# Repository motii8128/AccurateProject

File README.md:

# AccurateProject
2025年部内ロボコン「キアイダケ」チームのソフトウェア、ハードウェアについて

|name|link|
|:--:|:--:|
|マイコンソフトウェア|[AccurateHardware](https://github.com/motii8128/AccurateProject/tree/main/AccurateHardware)|
|制御基盤|[AccurateBoard](https://github.com/motii8128/AccurateProject/tree/main/Accurate)|
|電源基盤|[MainPowerSupplyer](https://github.com/motii8128/AccurateProject/tree/main/MainPowerSuppky)|
|分電基盤|[PowerDivider](https://github.com/motii8128/AccurateProject/tree/main/PowerDivider)|
|LED基盤|[led01](https://github.com/motii8128/AccurateProject/tree/main/led01)|

# マイコンソフトウェア「AccurateHardware」

# マイコン制御基盤「AccurateBoard」

# 電源基盤「MainPowerSupplyer」

# 分電基盤「PowerDivider」

# LED基盤「led01」

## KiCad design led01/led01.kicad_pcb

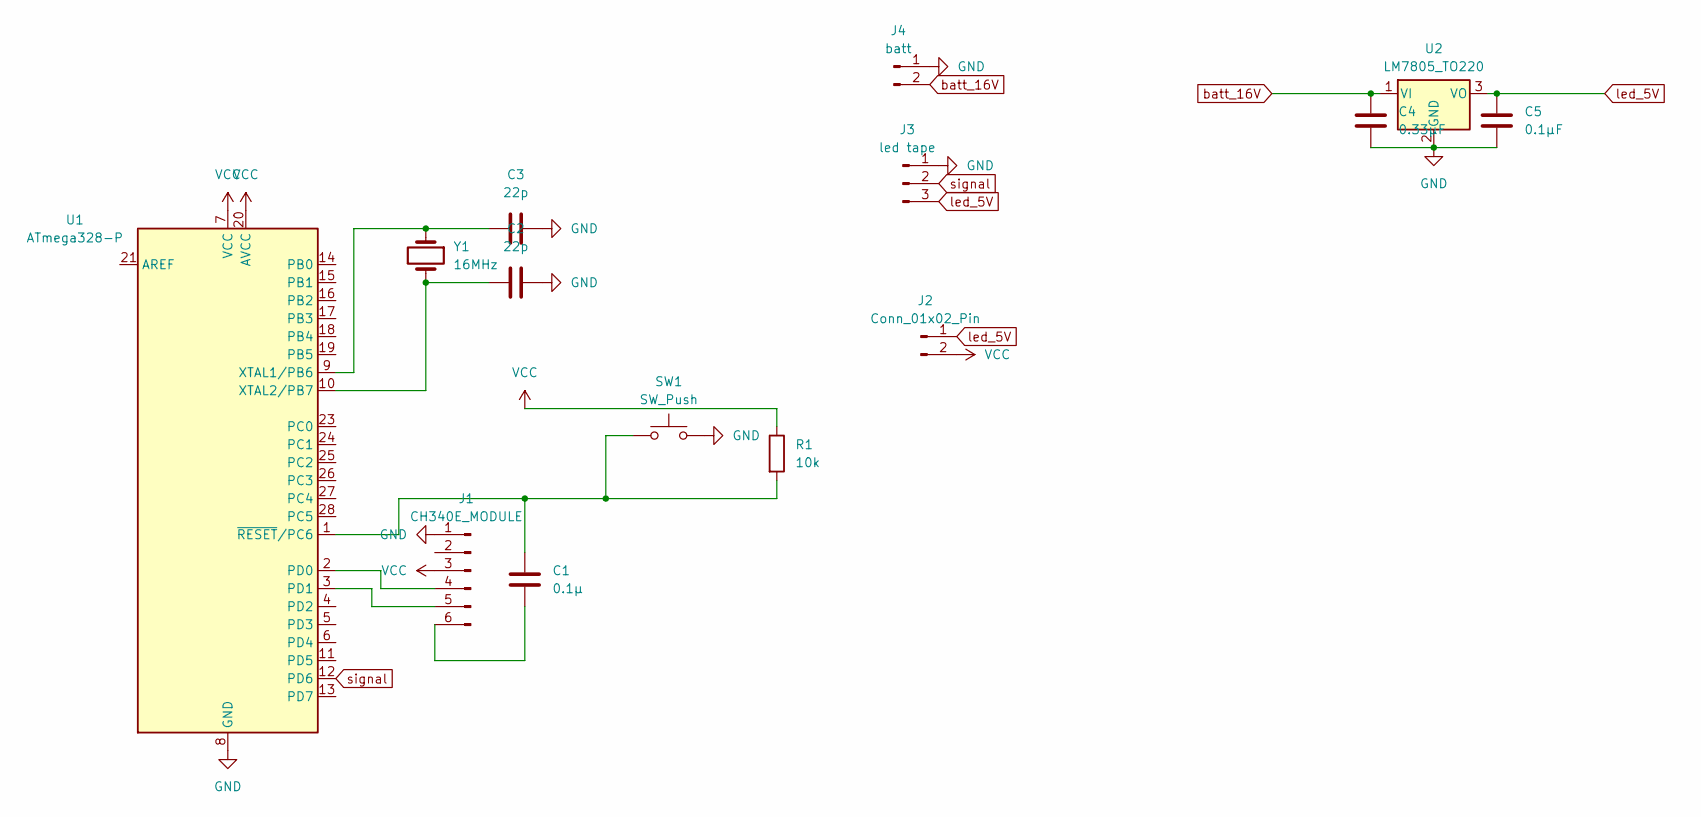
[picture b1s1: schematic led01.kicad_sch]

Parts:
C1: 0.1μ; C_Disc_D3.0mm_W2.0mm_P2.50mm
C2, C3: 22p; C_Disc_D3.0mm_W2.0mm_P2.50mm
C4: 0.33μF; C_Disc_D3.0mm_W2.0mm_P2.50mm
C5: 0.1μF; C_Disc_D3.0mm_W2.0mm_P2.50mm
J1: CH340E_MODULE; PinHeader_1x06_P2.54mm_Vertical
J2: Conn_01x02_Pin; PinHeader_1x02_P2.54mm_Vertical
J3: led tape; JST_XH_S3B-XH-A-1_1x03_P2.50mm_Horizontal
J4: batt; AMASS_XT30PW-M_1x02_P2.50mm_Horizontal
R1: 10k; R_Axial_DIN0207_L6.3mm_D2.5mm_P10.16mm_Horizontal
SW1: SW_Push; SW_PUSH_6mm
U1: ATmega328-P; DIP-28_W7.62mm
U2: LM7805_TO220; TO-220-3_Vertical
Y1: 16MHz; Crystal_HC18-U_Vertical

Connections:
GND: C2.2, C3.2, C4.2, C5.2, J1.1, J3.1, J4.1, SW1.2, U1.8 (GND), U1.22 (GND), U2.2 (GND)
unnamed: J1.4, U1.2 (PD0)
unnamed: J1.5, U1.3 (PD1)
unnamed: C1.2, J1.6
unnamed: C3.1, U1.9 (XTAL1/PB6), Y1.1
unnamed: C2.1, U1.10 (XTAL2/PB7), Y1.2
unnamed: C1.1, R1.2, SW1.1, U1.1 (~RESET/PC6)
VCC: J1.3, J2.2, R1.1, U1.7 (VCC), U1.20 (AVCC)
batt_16V: C4.1, J4.2, U2.1 (VI)
led_5V: C5.1, J2.1, J3.3, U2.3 (VO)
signal: J3.2, U1.12 (PD6)

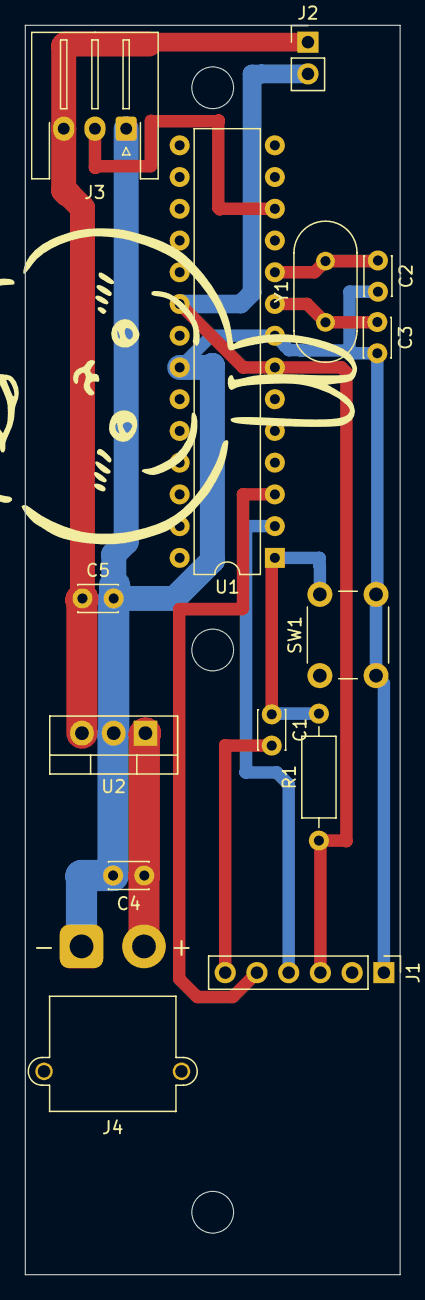
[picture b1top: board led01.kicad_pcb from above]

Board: 2 copper layers, 30.0 x 100.0 mm, 14 parts (0 on the bottom side), 11 nets.

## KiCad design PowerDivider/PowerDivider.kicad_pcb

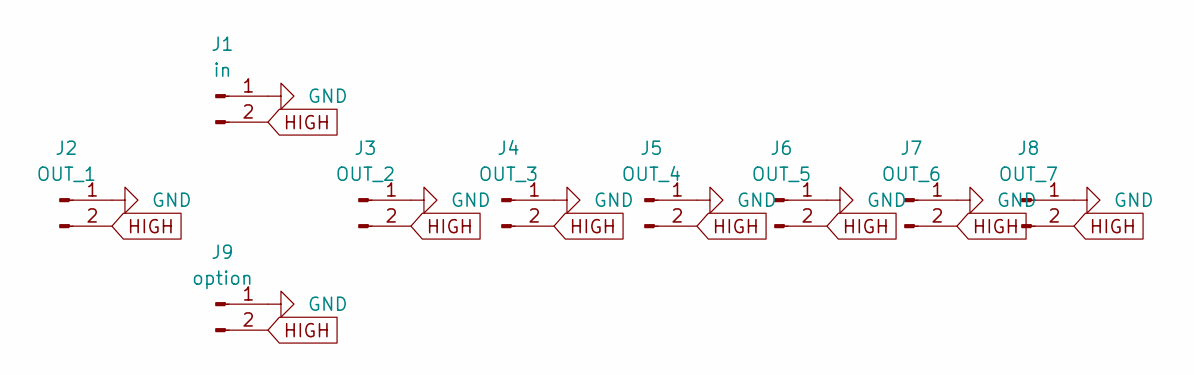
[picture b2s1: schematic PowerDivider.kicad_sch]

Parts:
J1: in; AMASS_XT30PW-M_1x02_P2.50mm_Horizontal
J2: OUT_1; AMASS_XT30PW-F_1x02_P2.50mm_Horizontal
J3: OUT_2; AMASS_XT30PW-F_1x02_P2.50mm_Horizontal
J4: OUT_3; AMASS_XT30PW-F_1x02_P2.50mm_Horizontal
J5: OUT_4; AMASS_XT30PW-F_1x02_P2.50mm_Horizontal
J6: OUT_5; AMASS_XT30PW-F_1x02_P2.50mm_Horizontal
J7: OUT_6; AMASS_XT30PW-F_1x02_P2.50mm_Horizontal
J8: OUT_7; AMASS_XT30PW-F_1x02_P2.50mm_Horizontal
J9: option; AMASS_XT30PW-M_1x02_P2.50mm_Horizontal

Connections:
GND: J1.1, J2.1, J3.1, J4.1, J5.1, J6.1, J7.1, J8.1, J9.1
HIGH: J1.2, J2.2, J3.2, J4.2, J5.2, J6.2, J7.2, J8.2, J9.2

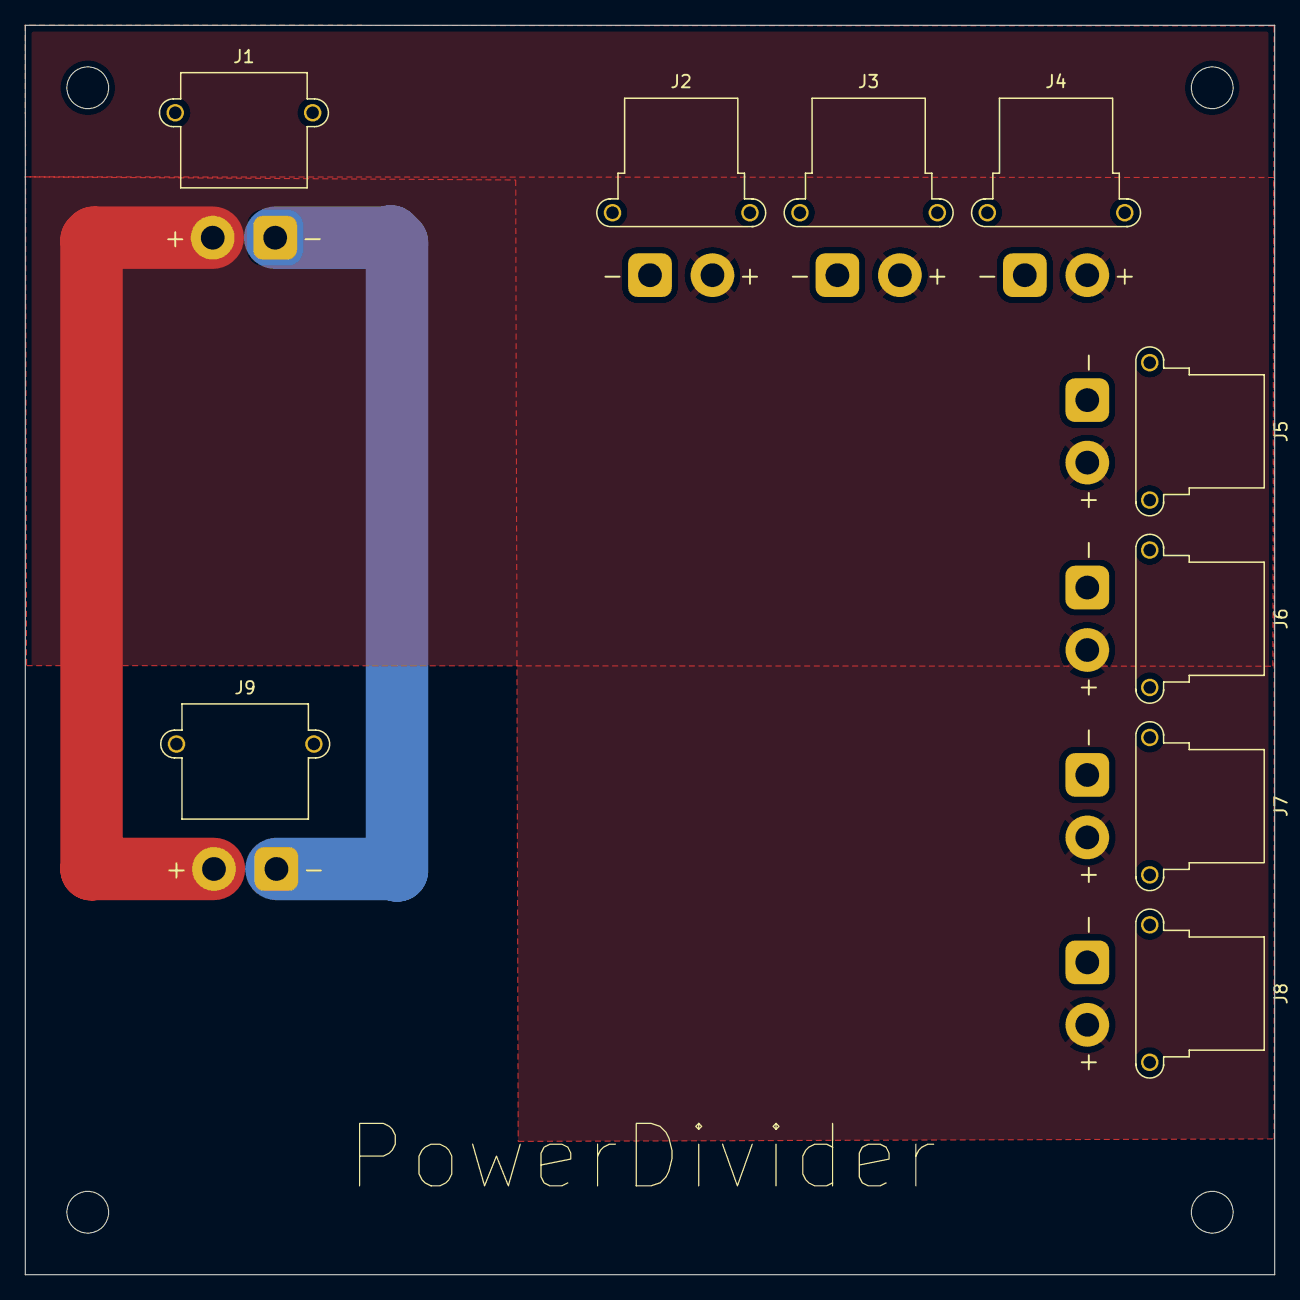
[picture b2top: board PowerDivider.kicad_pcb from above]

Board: 2 copper layers, 100.0 x 100.0 mm, 9 parts (0 on the bottom side), 2 nets.

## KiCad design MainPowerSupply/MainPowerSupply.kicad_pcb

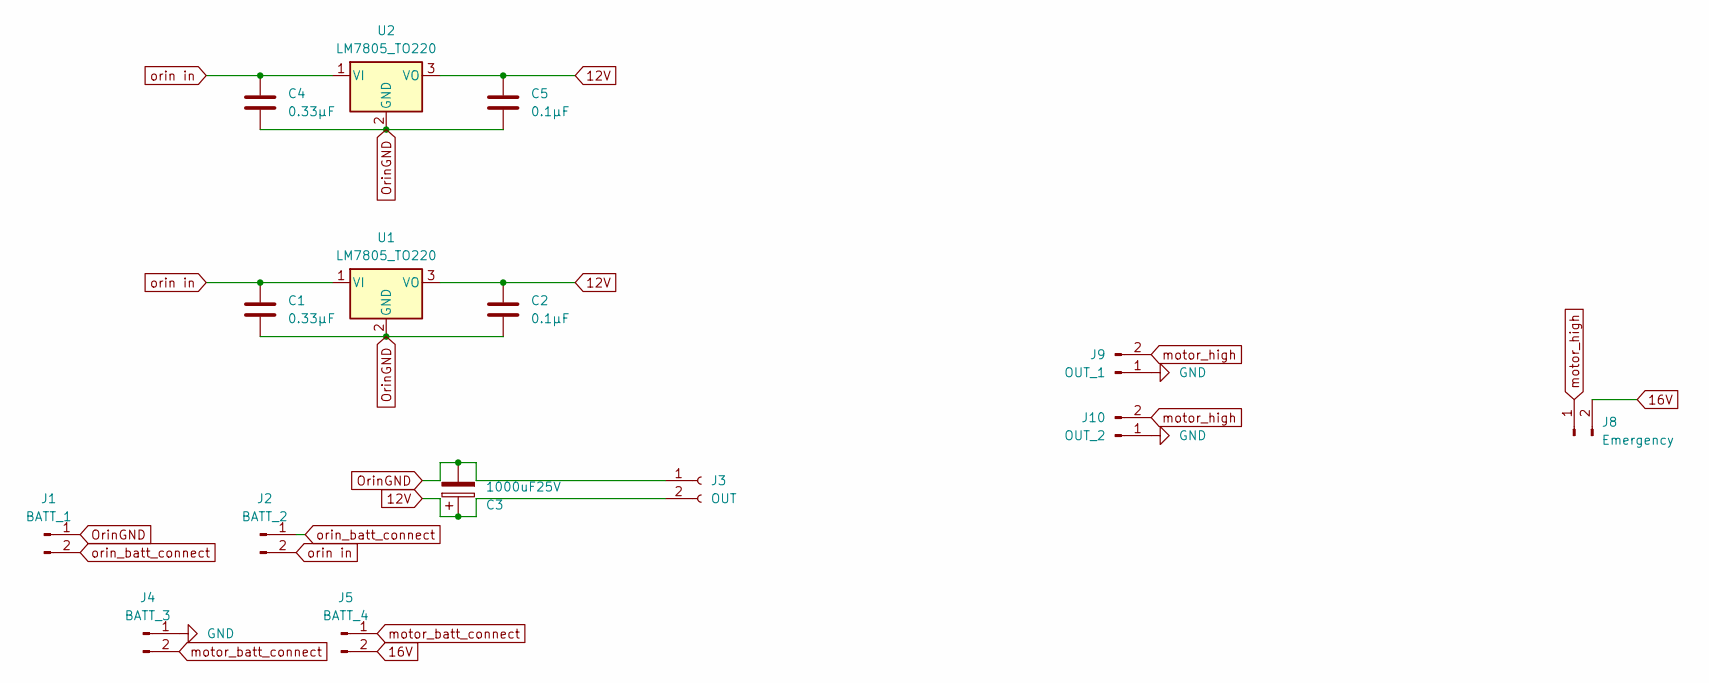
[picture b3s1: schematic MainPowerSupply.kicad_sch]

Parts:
C1, C4: 0.33μF; C_Disc_D3.0mm_W2.0mm_P2.50mm
C2, C5: 0.1μF; C_Disc_D3.0mm_W2.0mm_P2.50mm
C3: 1000uF25V; CP_Radial_D10.0mm_P5.00mm
J1: BATT_1; AMASS_XT60PW-M_1x02_P7.20mm_Horizontal
J2: BATT_2; AMASS_XT60PW-M_1x02_P7.20mm_Horizontal
J3: OUT; AMASS_XT30PW-F_1x02_P2.50mm_Horizontal
J4: BATT_3; AMASS_XT60PW-M_1x02_P7.20mm_Horizontal
J5: BATT_4; AMASS_XT60PW-M_1x02_P7.20mm_Horizontal
J8: Emergency; AMASS_XT60PW-F_1x02_P7.20mm_Horizontal
J9: OUT_1; AMASS_XT30PW-M_1x02_P2.50mm_Horizontal
J10: OUT_2; AMASS_XT30PW-M_1x02_P2.50mm_Horizontal
U1, U2: LM7805_TO220; TO-220-3_Vertical

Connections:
12V: C2.1, C3.1, C5.1, J3.2, U1.3 (VO), U2.3 (VO)
16V: J5.2, J8.2
GND: J4.1, J9.1, J10.1
OrinGND: C1.2, C2.2, C3.2, C4.2, C5.2, J1.1, J3.1, U1.2 (GND), U2.2 (GND)
motor_batt_connect: J4.2, J5.1
motor_high: J8.1, J9.2, J10.2
orin in: C1.1, C4.1, J2.2, U1.1 (VI), U2.1 (VI)
orin_batt_connect: J1.2, J2.1

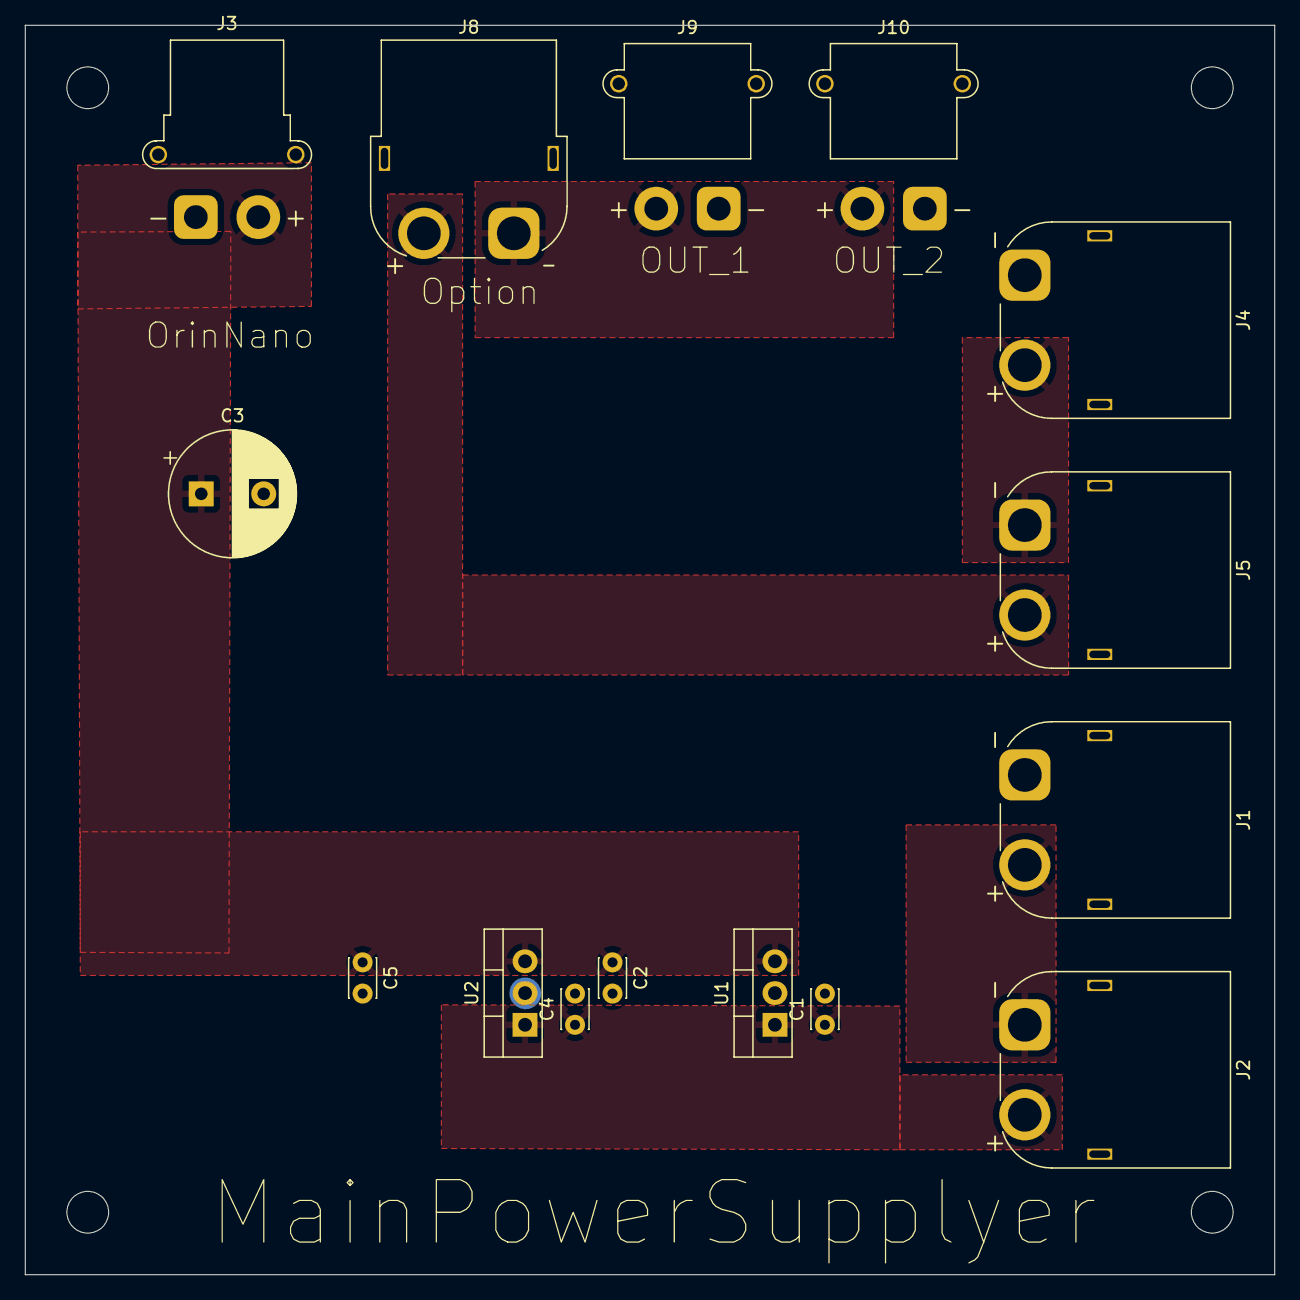
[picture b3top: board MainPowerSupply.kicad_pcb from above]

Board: 2 copper layers, 100.0 x 100.0 mm, 15 parts (0 on the bottom side), 8 nets.

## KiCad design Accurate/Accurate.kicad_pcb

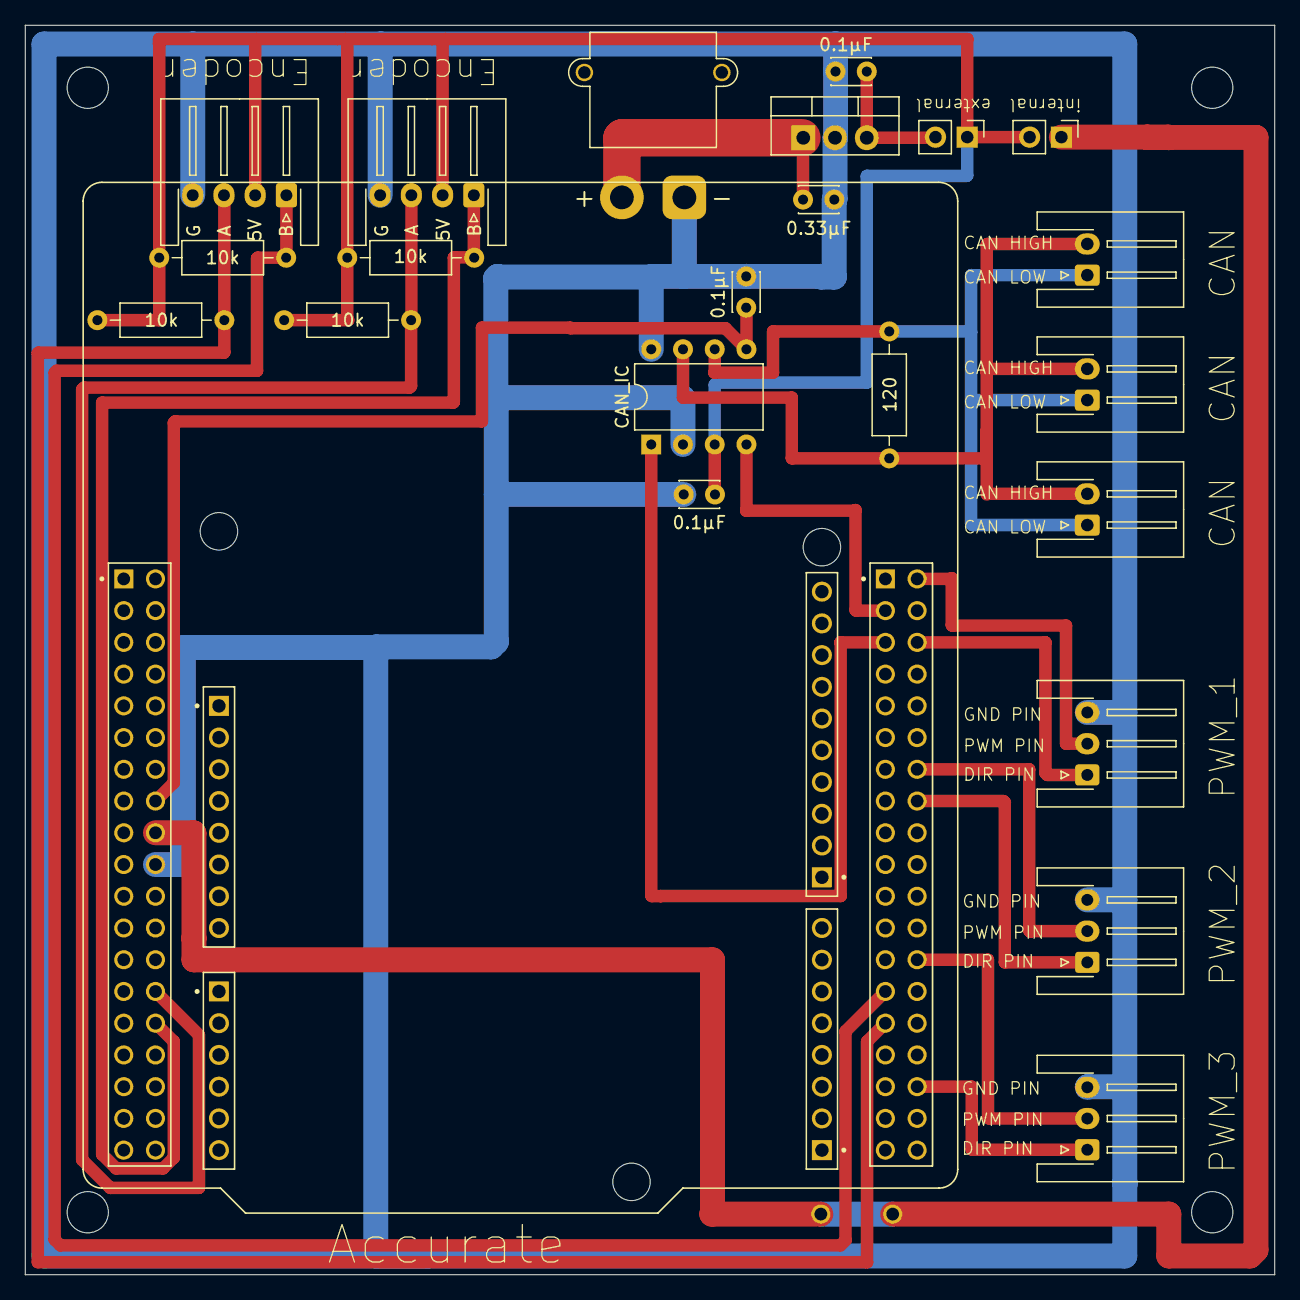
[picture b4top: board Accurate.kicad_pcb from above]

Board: 2 copper layers, 100.0 x 100.0 mm, 23 parts (0 on the bottom side), 19 nets.

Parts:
0.1μF, 0.1μF#2: 0.1μ; C_Disc_D3.0mm_W2.0mm_P2.50mm
0.33μF: 0.33μF; C_Disc_D3.0mm_W2.0mm_P2.50mm
10k, 10k#2, 10k#3, 10k#4: 10k; R_Axial_DIN0207_L6.3mm_D2.5mm_P10.16mm_Horizontal
120: 120; R_Axial_DIN0207_L6.3mm_D2.5mm_P10.16mm_Horizontal
C4: 0.1μF; C_Disc_D3.0mm_W2.0mm_P2.50mm
CAN_IC: MCP2562-E-P; DIP-8_W7.62mm
J1: CAN_1; JST_XH_S2B-XH-A-1_1x02_P2.50mm_Horizontal
J2: CAN_2; JST_XH_S2B-XH-A-1_1x02_P2.50mm_Horizontal
J3: CAN_3; JST_XH_S2B-XH-A-1_1x02_P2.50mm_Horizontal
J4: PWM_OUT_1; JST_XH_S3B-XH-A-1_1x03_P2.50mm_Horizontal
J5: PWM_OUT_2; JST_XH_S3B-XH-A-1_1x03_P2.50mm_Horizontal
J6: PWM_OUT_3; JST_XH_S3B-XH-A-1_1x03_P2.50mm_Horizontal
J7: Encoder_1; JST_XH_S4B-XH-A-1_1x04_P2.50mm_Horizontal
J8: Encoder_2; JST_XH_S4B-XH-A-1_1x04_P2.50mm_Horizontal
J9: BATT_IN; AMASS_XT30PW-M_1x02_P2.50mm_Horizontal
J10, J11: Conn_01x02_Pin; PinHeader_1x02_P2.54mm_Vertical
U1: LM7805_TO220; TO-220-3_Vertical
U3: NUCLEO-F446RE; MODULE_NUCLEO-F446RE

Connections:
3.3V: 0.1μF#2.1, CAN_IC.5 (Vio), U3.CN7_16 (CN7_+3V3)
5V: 0.1μF.1, 10k.1, 10k#2.1, 10k#3.1, 10k#4.1, C4.1, CAN_IC.3 (VDD), J7.2, J8.2, J10.2, J11.1, J11.2, U1.3 (VO)
16V: 0.33μF.1, J9.2, U1.1 (VI)
CAN_H: 120.1, CAN_IC.7 (CANH), J1.2, J2.2, J3.2
CAN_L: 120.2, CAN_IC.6 (CANL), J1.1, J2.1, J3.1
DIR_1: J4.1, U3.CN10_6 (PC5)
DIR_2: J5.1, U3.CN10_16 (PB12)
DIR_3: J6.1, U3.CN10_34 (PC4)
GND: 0.1μF.2, 0.1μF#2.2, 0.33μF.2, C4.2, CAN_IC.2 (VSS), CAN_IC.8 (STBY), J4.3, J5.3, J6.3, J7.4, J8.4, J9.1, U1.2 (GND), U3.CN7_19 (CN7_GND__1), U3.CN7_20 (CN7_GND__2), U3.CN7_22 (CN7_GND__3), U3.CN10_9 (CN10_GND)
PWM_1: J4.2, U3.CN10_2 (PC8)
PWM_2: J5.2, U3.CN10_14 (PA11)
PWM_3: J6.2, U3.CN10_26 (PB15)
RX: CAN_IC.4 (RXD), U3.CN10_3 (PB8)
TX: CAN_IC.1 (TXD), U3.CN10_5 (PB9)
encode_1A: 10k#4.2, J7.3, U3.CN7_28 (PA0)
encode_1B: 10k#3.2, J7.1, U3.CN7_30 (PA1)
encode_2A: 10k#2.2, J8.1, U3.CN10_27 (PB4)
encode_2B: 10k.2, J8.3, U3.CN10_29 (PB5)
mc_5v: J10.1, U3.CN7_18 (CN7_+5V)

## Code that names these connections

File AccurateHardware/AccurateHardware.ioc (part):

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Mcu.Name=STM32F446R(C-E)Tx
Mcu.Package=LQFP64
Mcu.UserName=STM32F446RETx
PA1.GPIOParameters=GPIO_Speed
PA1.GPIO_Speed=GPIO_SPEED_FREQ_VERY_HIGH
PA1.Signal=S_TIM2_CH2
PA11.Signal=S_TIM1_CH4
PA13.GPIOParameters=GPIO_Label
PA13.GPIO_Label=TMS
PA13.Mode=Serial_Wire
PA13.Signal=SYS_JTMS-SWDIO
PA14.GPIOParameters=GPIO_Label
PA14.GPIO_Label=TCK
PA14.Mode=Serial_Wire
PA14.Signal=SYS_JTCK-SWCLK
PA2.Mode=Asynchronous
PA2.Signal=USART2_TX
PA3.Mode=Asynchronous
PA3.Signal=USART2_RX
PA5.GPIOParameters=GPIO_Speed
PA5.GPIO_Speed=GPIO_SPEED_FREQ_VERY_HIGH
PA5.Signal=S_TIM2_CH1_ETR
PB12.GPIOParameters=GPIO_Label
PB12.GPIO_Label=DIR_2
PB12.Signal=GPIO_Output
PB15.GPIOParameters=GPIO_Label
PB15.GPIO_Label=PWM_3
PB15.Signal=S_TIM12_CH2
PB3.GPIOParameters=GPIO_Label
PB3.GPIO_Label=SWO
PB3.Signal=SYS_JTDO-SWO
PB4.Signal=S_TIM3_CH1
PB5.Signal=S_TIM3_CH2
PB8.Mode=CAN_Activate
PB8.Signal=CAN1_RX
PB9.Mode=CAN_Activate
PB9.Signal=CAN1_TX
PC14-OSC32_IN.Mode=LSE-External-Oscillator
PC14-OSC32_IN.Signal=RCC_OSC32_IN
PC15-OSC32_OUT.Mode=LSE-External-Oscillator
PC15-OSC32_OUT.Signal=RCC_OSC32_OUT
PC4.GPIOParameters=GPIO_Label
PC4.GPIO_Label=DIR_3
PC4.Signal=GPIO_Output
PC5.GPIOParameters=GPIO_Label
PC5.GPIO_Label=DIR_1
PC5.Signal=GPIO_Output
PC8.GPIOParameters=GPIO_Label
PC8.GPIO_Label=PWM_1
PC8.Signal=S_TIM8_CH3
PH0-OSC_IN.Mode=HSE-External-Oscillator
PH0-OSC_IN.Signal=RCC_OSC_IN
PH1-OSC_OUT.Mode=HSE-External-Oscillator
PH1-OSC_OUT.Signal=RCC_OSC_OUT
RCC.HSE_VALUE=8000000
RCC.SYSCLKFreq_VALUE=180000000
RCC.SYSCLKSource=RCC_SYSCLKSOURCE_PLLCLK
board=NUCLEO-F446RE
boardIOC=true

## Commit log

2025-02-17 update code
2025-02-21 Rename Screenshot from 2025-02-21 13-09-25.png to led01.png
2025-03-16 biggest update
